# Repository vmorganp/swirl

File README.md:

# Swirl
A Split keyboard with a thumb encoder on either side heavily inspired by the [helix](https://github.com/MakotoKurauchi/helix)

# ToDo
- diconnect the 2 pairs of inner pins on the trrs jack. both being ground causes a short circuit and requires modification of the TRRS jack at this time
    - I'm pretty sure there's something i2c related with this that you're *supposed* to do, but I don't actually understand that.
- Get the button part of the encoder in the appropriate col/row rather than being it's own direct connect key which is poorly supported in qmk

# Build Guide
## Ingredients
- 2x PCBs (Upload the zip from [here](./v0/ergogen_output/gerber.zip) to https://jlcpcb.com/ (the minimum order quantity is 5, maybe get six and share with a couple friends?)
- 2x Pro-micro or pro-micro-compatible microcontrollers (I like the elite pi from [here](https://www.littlekeyboards.com/products/elite-pi))
- 70x 1N4148 surface mounted diodes (SMD) like [these](https://www.diykeyboards.com/parts/product/p1n4148-smd-diodes-10pcs) (you actually only need 64, but they're almost always sold in 10s)
- 70x kailh choc v1 keyswitches of your choice like [these](https://www.littlekeyboards.com/collections/keyboard-switches/products/kailh-choc-low-profile-switches) (you actually only need 64, but they're almost always sold in 10s)
- 70x kailh choc v1 key caps of your choice like [these](https://www.littlekeyboards.com/collections/keycaps/products/mbk-choc-low-profile-keycaps?variant=39466488660035) (you actually only need 64, but they're almost always sold in 10s)
- 2x 3.5mm trrs headphone jack like [these](https://www.diykeyboards.com/parts/product/pj320a)
- 2x If you don't use the elite pi or have a will to do paperclip-resets, get some reset switches like [these](https://www.diykeyboards.com/parts/electronics/product/p3-5-x-6mm-vertical-tactile-microswitch)
- 2x EVQWGD001 roller encoder like [these](https://www.amazon.com/Encoder-Wheel-Switch-6-pin-EVQWGD001/dp/B0995GCFSX/ref=sr_1_2?keywords=EVQWGD001&sr=8-2) (please don't buy these on amazon, try ebay or something because these are wildly overpriced, but this link should be more stable than an ebay listing)
- Soldering tools
- Optionally, all of the hotswap stuff for your controllers and switches

## Hardware Steps
1. Bridge the microcontroller connections depending on your controller's orientation
    If you want the smooth side up, solder the bridges on the bottom, if you want the components (and the reset button on an eliete-pi) facing up, solder the bridges that face up
1. Solder SMDs (Ensure that the line on the SMD is on the same side of the connection as the line printed on the PCB)
1. Solder microcontroller
1. Solder TRRS connector
1. Solder key switches
1. Solder roller encoder

## Software Steps
Prerequisites
- Have qmk installed and setup, try the docs [here](https://docs.qmk.fm/#/newbs_getting_started) if you don't already have that setup

1. clone my qmk fork (maybe we get this merged into upstream at some point??)
`git clone git@github.com:vmorganp/qmk_firmware.git`

1. Compile and flash the firmware. (The default firmware is NOT good and I highly recommend creating your own)
    - Assuming you're using an elite-pi, compile the firmware using:
        1. qmk compile -kb swirl -km default -e CONVERT_TO=elite_pi`
        1. Drag and drop the compiled <filename>.uf2 file onto the pi

    - Otherwise:
        1. Run `qmk flash -kb swirl -km default`
        1. press the reset button/bridge the reset contact
        1. let it run

1. enjoy!

# Credits
@mrzealot and the other maintainers of ergogen

@ceoloide for having ergogen v4 footprints over in https://github.com/ceoloide/corney-island

@superfola on discord for helping me find me the reversible encoder footprint

@benvallack for informing me in a digestible way that this whole thing is actually doable

@imstubtw (i think) for the tutorial at https://flatfootfox.com/ergogen-part4-footprints-cases/

@aejay for the "swirl" text graphic [here](./graphics/swirl_text.svg)

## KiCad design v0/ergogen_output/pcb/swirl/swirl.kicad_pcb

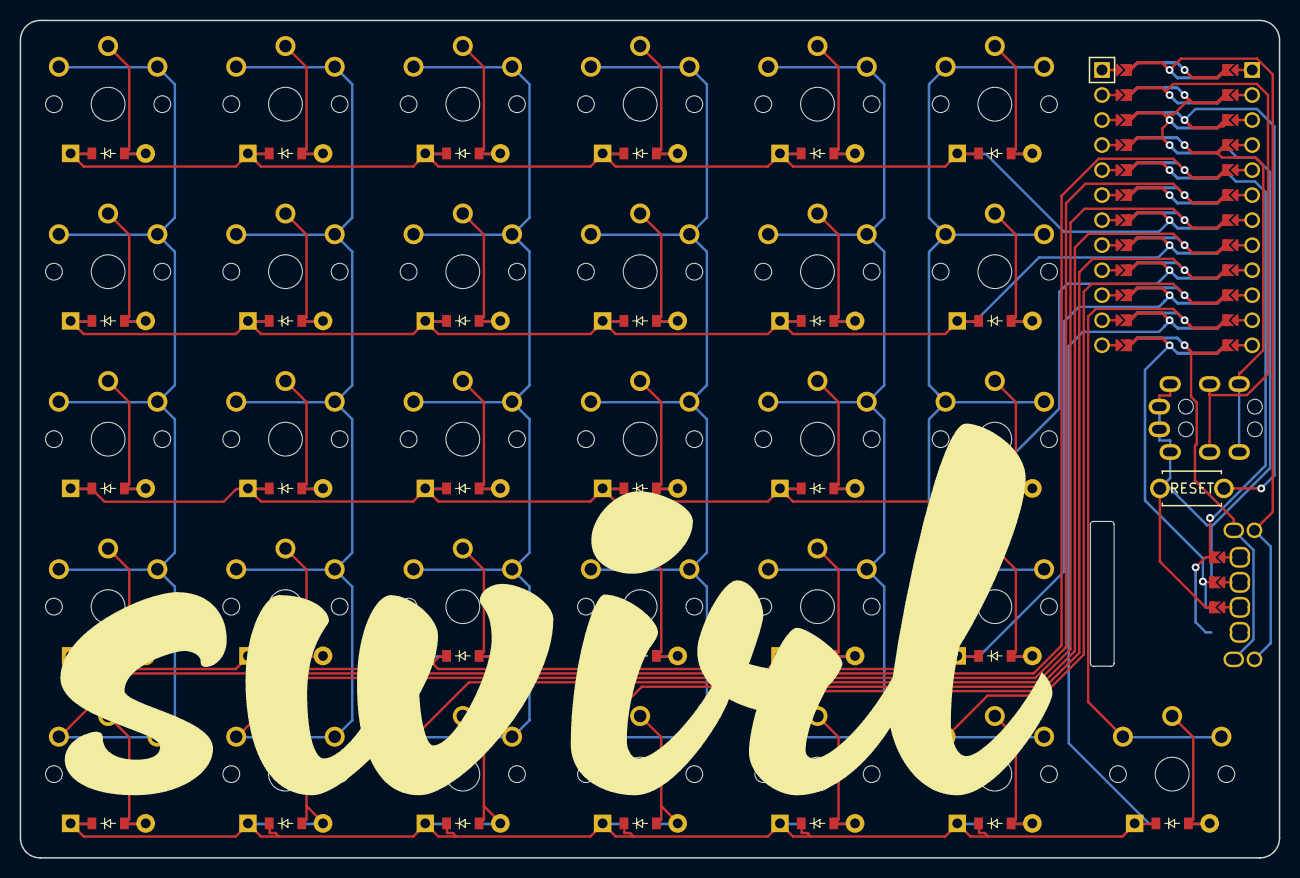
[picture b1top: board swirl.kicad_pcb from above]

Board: 2 copper layers, 127.8 x 85.0 mm, 66 parts (0 on the bottom side), 51 nets.

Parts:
B1: ResetSW
D1, D2, D3, D4, D5, D6, D7, D8, D9, D10, D11, D12, D13, D14, D15, D16, D17, D18, D19, D20, D21, D22, D23, D24, D25, D26, D27, D28, D29, D30, D31: ComboDiode
EN1: EVQWGD001; RollerEncoder
MCU1: ProMicro
S1, S2, S3, S4, S5, S6, S7, S8, S9, S10, S11, S12, S13, S14, S15, S16, S17, S18, S19, S20, S21, S22, S23, S24, S25, S26, S27, S28, S29, S30, S31: PG1350
TRRS1: TRRS-PJ-320A-dual

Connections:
GND: B1.1, EN1.C, MCU1.2, MCU1.21, MCU1.22, TRRS1.1, TRRS1.2
MISO: MCU1.10, S26.1, S27.1, S28.1, S29.1, S30.1
MOSI: MCU1.11, S31.1
P0: MCU1.23, TRRS1.3
P1: EN1.S1, MCU1.24
P4: D5.1, D10.1, D15.1, D20.1, D25.1, D30.1, MCU1.18
P5: D4.1, D9.1, D14.1, D19.1, D24.1, D29.1, MCU1.17
P6: D3.1, D8.1, D13.1, D18.1, D23.1, D28.1, MCU1.16
P7: D2.1, D7.1, D12.1, D17.1, D22.1, D27.1, MCU1.15
P8: D1.1, D6.1, D11.1, D16.1, D21.1, D26.1, D31.1, MCU1.14
P9: EN1.B, MCU1.13
P10: EN1.S2, MCU1.12
P18: MCU1.8, S16.1, S17.1, S18.1, S19.1, S20.1
P19: MCU1.7, S11.1, S12.1, S13.1, S14.1, S15.1
P20: MCU1.6, S6.1, S7.1, S8.1, S9.1, S10.1
P21: MCU1.5, S1.1, S2.1, S3.1, S4.1, S5.1
RST: B1.2, MCU1.3
SCLK: MCU1.9, S21.1, S22.1, S23.1, S24.1, S25.1
SDA: EN1.A, MCU1.20
VCC: MCU1.4, TRRS1.4
extraInner_mod: D31.2, S31.2
index_bottom: D22.2, S22.2
index_home: D23.2, S23.2
index_mod: D21.2, S21.2
index_num: D25.2, S25.2
index_top: D24.2, S24.2
inner_bottom: D27.2, S27.2
inner_home: D28.2, S28.2
inner_mod: D26.2, S26.2
inner_num: D30.2, S30.2
inner_top: D29.2, S29.2
middle_bottom: D17.2, S17.2
middle_home: D18.2, S18.2
middle_mod: D16.2, S16.2
middle_num: D20.2, S20.2
middle_top: D19.2, S19.2
outer_bottom: D2.2, S2.2
outer_home: D3.2, S3.2
outer_mod: D1.2, S1.2
outer_num: D5.2, S5.2
outer_top: D4.2, S4.2
pinky_bottom: D7.2, S7.2
pinky_home: D8.2, S8.2
pinky_mod: D6.2, S6.2
pinky_num: D10.2, S10.2
pinky_top: D9.2, S9.2
ring_bottom: D12.2, S12.2
ring_home: D13.2, S13.2
ring_mod: D11.2, S11.2
ring_num: D15.2, S15.2
ring_top: D14.2, S14.2

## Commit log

2023-06-21 ergogen goodies, still have to manully drop in and route the encoder
2023-06-21 formatting
2023-06-28 fix 90 degree bend, general cleanup
2023-06-29 repack updated gerbers
2023-07-07 Add drill files, make serial component use serial pin
2023-07-08 big fat readme upgrade
2023-07-22 fix some wiring, add some graphics, move some stuff to more convenient palces
2023-07-22 credits
2023-08-11 README updates
